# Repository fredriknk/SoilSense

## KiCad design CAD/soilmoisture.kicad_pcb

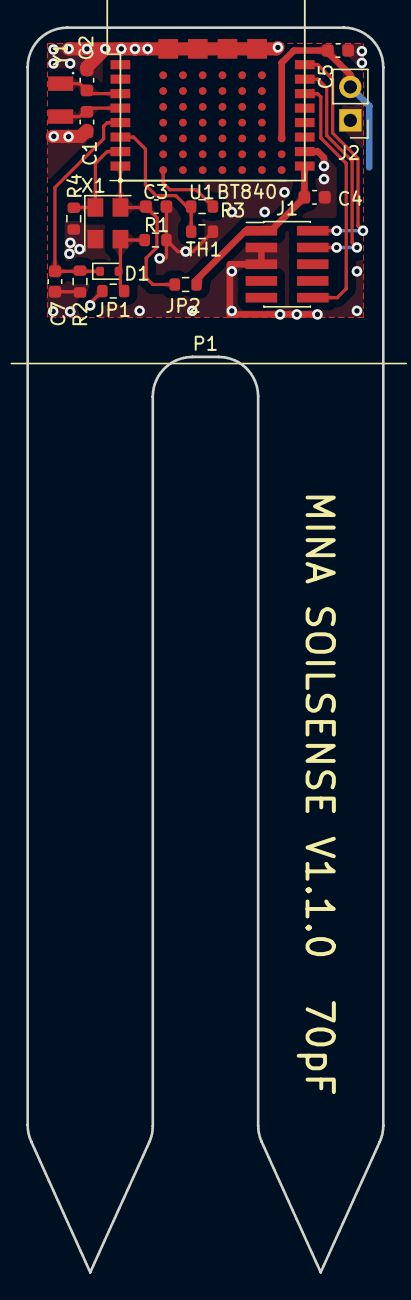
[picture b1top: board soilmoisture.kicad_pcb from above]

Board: 4 copper layers, 27.0 x 94.5 mm, 21 parts (1 on the bottom side), 15 nets.

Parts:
C1, C2: 12pF 0603; C_0603_1608Metric
C3, C7: 100nF 0603; C_0603_1608Metric
C4, C5: 4.7uf 0603; C_0603_1608Metric
D1: CDSU101A; D_SOD-523
J1: Conn_ARM_JTAG_SWD_10; PinHeader_2x05_P1.27mm_Vertical_SMD
J2: Conn_01x02 0.1"; PinHeader_1x02_P2.54mm_Vertical
JP1, JP2: 0R 0603; R_0603_1608Metric
P1: 1-30pf; 1-70pf_Soil_Probe
R1, R2, R3, R4: 100k 0603 1%; R_0603_1608Metric
TH1: 100k NTC; R_0603_1608Metric
U1: BT840; BT840-BT840
U2: BAT-HLD-001
X1: SIT8008BC-23-18E-80.000000; Oscillator_SMD_SeikoEpson_SG8002CE-4Pin_3.2x2.5mm
Y1: ABS07-32.768KHZ-T; XTAL320X150X90

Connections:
+BATT: C5.1, J2.2, U1.P$F4 (F4/VDDH), U2.+@2
/NTC_POWER: R3.1, U1.P$Z6 (Z6/P106)
/Oscillator/ADC_OUT: C7.1, D1.1 (K), R2.1, U1.P$5 (P02/AIN0)
/Oscillator/Probe: JP1.2 (B), P1.1
/Oscillator/enable: R4.1, U1.P$7 (P09), X1.1 (EN)
/Oscillator/gpio_power: C3.1, JP2.1 (A), U1.P$8 (P10), X1.4 (Vdd)
/SWDCLK: J1.4 (SWDCLK/TCK), U1.P$15 (SWCLK)
/SWDIO: J1.2 (SWDIO/TMS), U1.P$16 (SWDIO)
/XL1: C2.2, U1.P$3 (P00/XL1), Y1.1
/XL2: C1.2, U1.P$4 (P01/XL2), Y1.2
/nRST: J1.10 (~RESET), U1.P$14 (P21/RESET)
GND: C1.1, C2.1, C3.2, C4.2, C5.2, C7.2, J1.3 (GND), J1.5 (GND), J2.1, P1.2, R1.2, R2.2, R4.2, TH1.2, U1.P$10 (GND), U1.P$F0 (F0/GND), U1.P$F1 (F1/GND), U1.P$F2 (F2/GND), U1.P$F3 (F3/GND), U2.-, X1.2 (GND)
NTC_ADC: R3.2, TH1.1, U1.P$6 (P03/AIN1)
unnamed: D1.2 (A), JP1.1 (A), R1.1, X1.3 (OUT)
VDD: C4.1, J1.1 (VCC), JP2.2 (B), U1.P$9 (VDD)

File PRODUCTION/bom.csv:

Designator,Footprint,Quantity,Value,LCSC Part #
"C1, C2",0603,2,12pF 0603,0603N120J500CT
"C3, C7",0603,2,100nF 0603,CL10B104KB8NNWC
"C4, C5",0603,2,4.7uf 0603,CL10A475KQ8NNNC
D1,D_SOD-523,1,CDSU101A,CDSU101A
J1,PinHeader_2x05_P1.27mm_Vertical_SMD,1,Conn_ARM_JTAG_SWD_10,20021121-00010C4LF
J2,PinHeader_1x02_P2.54mm_Vertical,1,"Conn_01x02 0.1""",61300211121
"JP1, JP2",0603,2,0R 0603,RMCF0603ZT0R00
"R1, R2, R3, R4",0603,4,100k 0603 1%,RC0603FR-07100KL
TH1,0603,1,100k NTC,ERT-J1VS104HA
U1,BT840-BT840,1,BT840,BT840
U2,BAT-HLD-001,1,BAT-HLD-001,BAT-HLD-001-TR
X1,Oscillator_SMD_SeikoEpson_SG8002CE-4Pin_3.2x2.5mm,1,SIT8008BC-23-18E-80.000000,SIT8008BC-23-18E-80.000000
Y1,XTAL320X150X90,1,ABS07-32.768KHZ-T,ABS07-32.768KHZ-T

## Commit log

2023-05-02 Update LICENSE
2023-05-02 Feat: First push
2023-05-02 Feat: Added real pictures EC production
2023-05-02 Fix: Type in file extension
2023-05-23 Feat: First working rust dev
2023-05-24 Feat: Gor probe-run working
2023-05-24 Feat: First real program
2023-05-24 Testing boarddefinition
2023-05-24 Soilsense
2023-05-24 kind of working
2023-05-26 blinktest
2023-05-26 Feat: Added inductor
2023-05-26 working proto
2023-06-01 Feat: WIP
2023-06-01 Feat: Removed submodules
2024-09-27 Latest
